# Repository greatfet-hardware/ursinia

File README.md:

# Ursinia
## a Grove base neighbor for GreatFET

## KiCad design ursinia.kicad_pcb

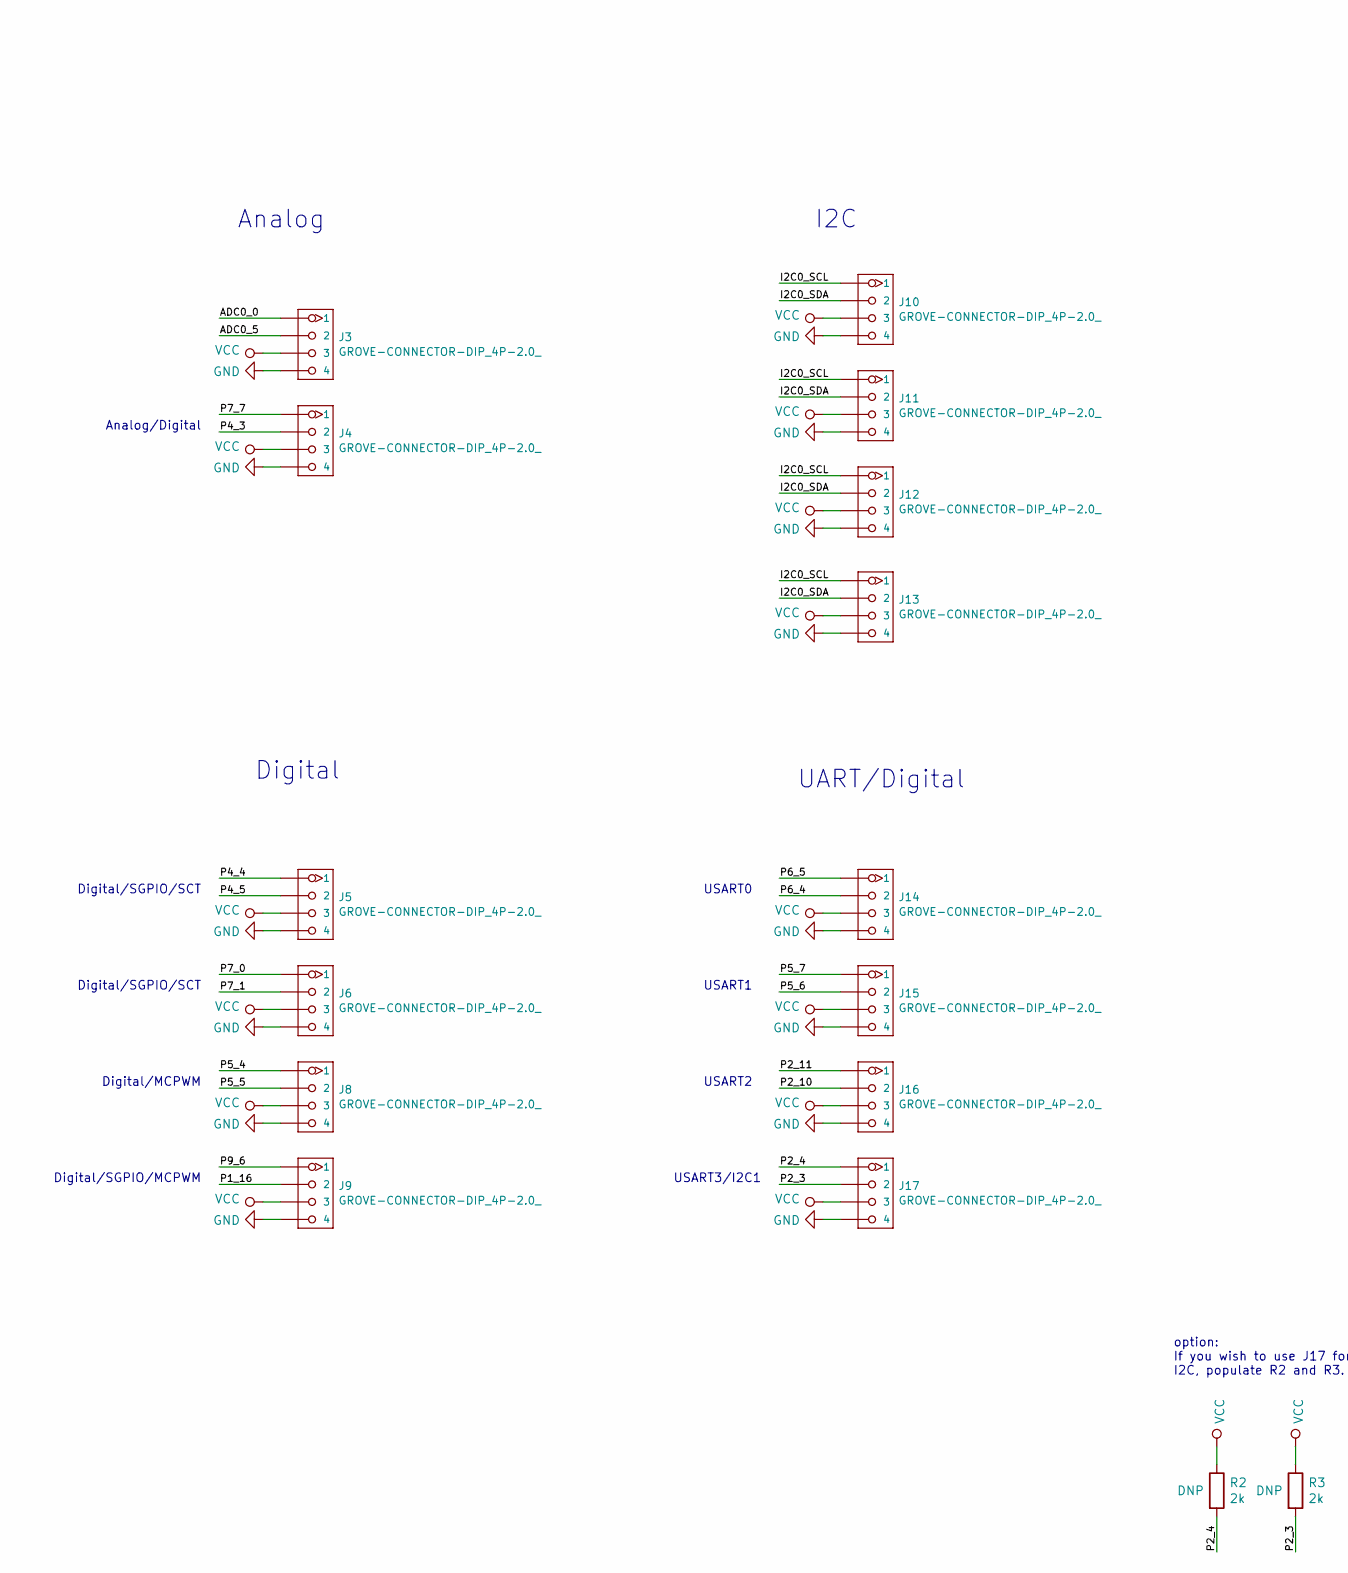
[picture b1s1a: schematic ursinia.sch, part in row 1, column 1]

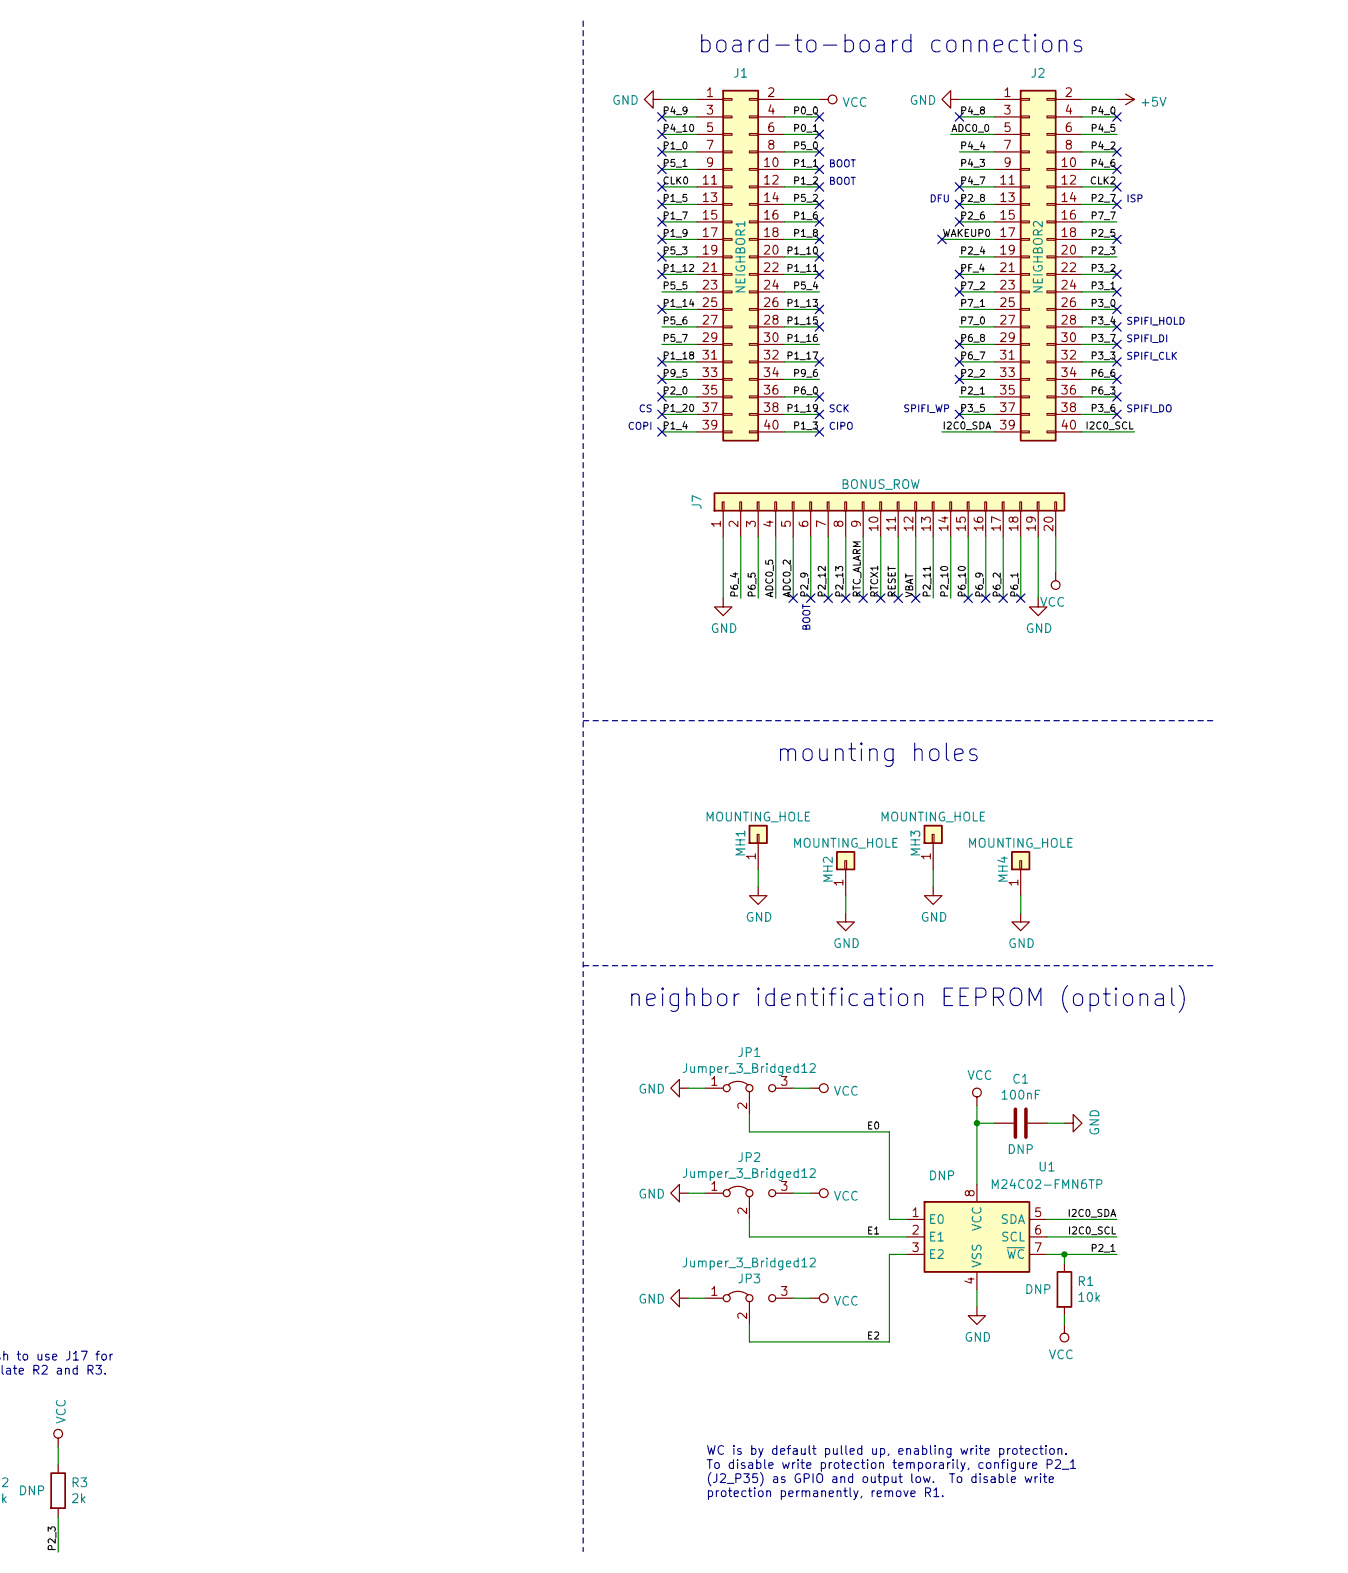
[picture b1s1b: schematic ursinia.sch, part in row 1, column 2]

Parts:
C1: 100nF; C_0603_1608Metric_Pad1.05x0.95mm_HandSolder
J1: NEIGHBOR1; HEADER-2x20; Part Number SSQ-120-23-G-D
J2: NEIGHBOR2; HEADER-2x20; Part Number SSQ-120-23-G-D
J3, J4, J9, J13, J17: GROVE-CONNECTOR-DIP_4P-2.0_; HW4-2.0-90D
J5, J6, J8, J10, J11, J12, J14, J15, J16: GROVE-CONNECTOR-DIP_4P-2.0_; HW4-2.0
J7: BONUS_ROW; HEADER-1x20; Part Number SSQ-120-23-G-S
JP1, JP2, JP3: Jumper_3_Bridged12; 0603-JUMPER-3-BRIDGED12
MH1, MH2, MH3, MH4: MOUNTING_HOLE; HOLE126MIL-COPPER
R1: 10k; R_0603_1608Metric_Pad1.05x0.95mm_HandSolder
R2, R3: 2k; R_0603_1608Metric_Pad1.05x0.95mm_HandSolder
U1: M24C02-FMN6TP; SOIC-8_3.9x4.9mm_P1.27mm

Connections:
+5V: J2.2
/ADC0_0: J2.5, J3.1
/ADC0_2: J7.5
/ADC0_5: J3.2, J7.4
/CLK0: J1.11
/CLK2: J2.12
/E0: JP1.2 (C), U1.1 (E0)
/E1: JP2.2 (C), U1.2 (E1)
/E2: JP3.2 (C), U1.3 (E2)
/I2C0_SCL: J2.40, J10.1, J11.1, J12.1, J13.1, U1.6 (SCL)
/I2C0_SDA: J2.39, J10.2, J11.2, J12.2, J13.2, U1.5 (SDA)
/P0_0: J1.4
/P0_1: J1.6
/P1_0: J1.7
/P1_1: J1.10
/P1_2: J1.12
/P1_3: J1.40
/P1_4: J1.39
/P1_5: J1.13
/P1_6: J1.16
/P1_7: J1.15
/P1_8: J1.18
/P1_9: J1.17
/P1_10: J1.20
/P1_11: J1.22
/P1_12: J1.21
/P1_13: J1.26
/P1_14: J1.25
/P1_15: J1.28
/P1_16: J1.30, J9.2
/P1_17: J1.32
/P1_18: J1.31
/P1_19: J1.38
/P1_20: J1.37
/P2_0: J1.35
/P2_1: J2.35, R1.1, U1.7 (~WC)
/P2_2: J2.33
/P2_3: J2.20, J17.2, R3.2
/P2_4: J2.19, J17.1, R2.2
/P2_5: J2.18
/P2_6: J2.15
/P2_7: J2.14
/P2_8: J2.13
/P2_9: J7.6
/P2_10: J7.14, J16.2
/P2_11: J7.13, J16.1
/P2_12: J7.7
/P2_13: J7.8
/P3_0: J2.26
/P3_1: J2.24
/P3_2: J2.22
/P3_3: J2.32
/P3_4: J2.28
/P3_5: J2.37
/P3_6: J2.38
/P3_7: J2.30
/P4_0: J2.4
/P4_2: J2.8
/P4_3: J2.9, J4.2
/P4_4: J2.7, J5.1
/P4_5: J2.6, J5.2
/P4_6: J2.10
/P4_7: J2.11
/P4_8: J2.3
/P4_9: J1.3
/P4_10: J1.5
/P5_0: J1.8
/P5_1: J1.9
/P5_2: J1.14
/P5_3: J1.19
/P5_4: J1.24, J8.1
/P5_5: J1.23, J8.2
/P5_6: J1.27, J15.2
/P5_7: J1.29, J15.1
/P6_0: J1.36
/P6_1: J7.18
/P6_2: J7.17
/P6_3: J2.36
/P6_4: J7.2, J14.2
/P6_5: J7.3, J14.1
/P6_6: J2.34
/P6_7: J2.31
/P6_8: J2.29
/P6_9: J7.16
/P6_10: J7.15
/P7_0: J2.27, J6.1
/P7_1: J2.25, J6.2
/P7_2: J2.23
/P7_7: J2.16, J4.1
/P9_5: J1.33
/P9_6: J1.34, J9.1
/PF_4: J2.21
/RESET: J7.11
/RTCX1: J7.10
/RTC_ALARM: J7.9
/VBAT: J7.12
/WAKEUP0: J2.17
GND: C1.1, J1.1, J2.1, J3.4, J4.4, J5.4, J6.4, J7.1, J7.19, J8.4, J9.4, J10.4, J11.4, J12.4, J13.4, J14.4, J15.4, J16.4, J17.4, JP1.1 (A), JP2.1 (A), JP3.1 (A), MH1.1, MH2.1, MH3.1, MH4.1, U1.4 (VSS)
VCC: C1.2, J1.2, J3.3, J4.3, J5.3, J6.3, J7.20, J8.3, J9.3, J10.3, J11.3, J12.3, J13.3, J14.3, J15.3, J16.3, J17.3, JP1.3 (B), JP2.3 (B), JP3.3 (B), R1.2, R2.1, R3.1, U1.8 (VCC)

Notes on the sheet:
CIPO
COPI
SCK
ISP
DFU
BOOT
WC is by default pulled up, enabling write protection. To disable write protection temporarily, configure P2_1 (J2_P35) as GPIO and output low. To disable write protection permanently, remove R1.
SPIFI_CLK
SPIFI_HOLD
SPIFI_WP
SPIFI_DO
SPIFI_DI
board-to-board connections
mounting holes
neighbor identification EEPROM (optional)
Analog
I2C
Digital
USART3/I2C1
USART2
USART1
USART0
UART/Digital
Analog/Digital
Digital/SGPIO/MCPWM
Digital/MCPWM
Digital/SGPIO/SCT
option: If you wish to use J17 for I2C, populate R2 and R3.

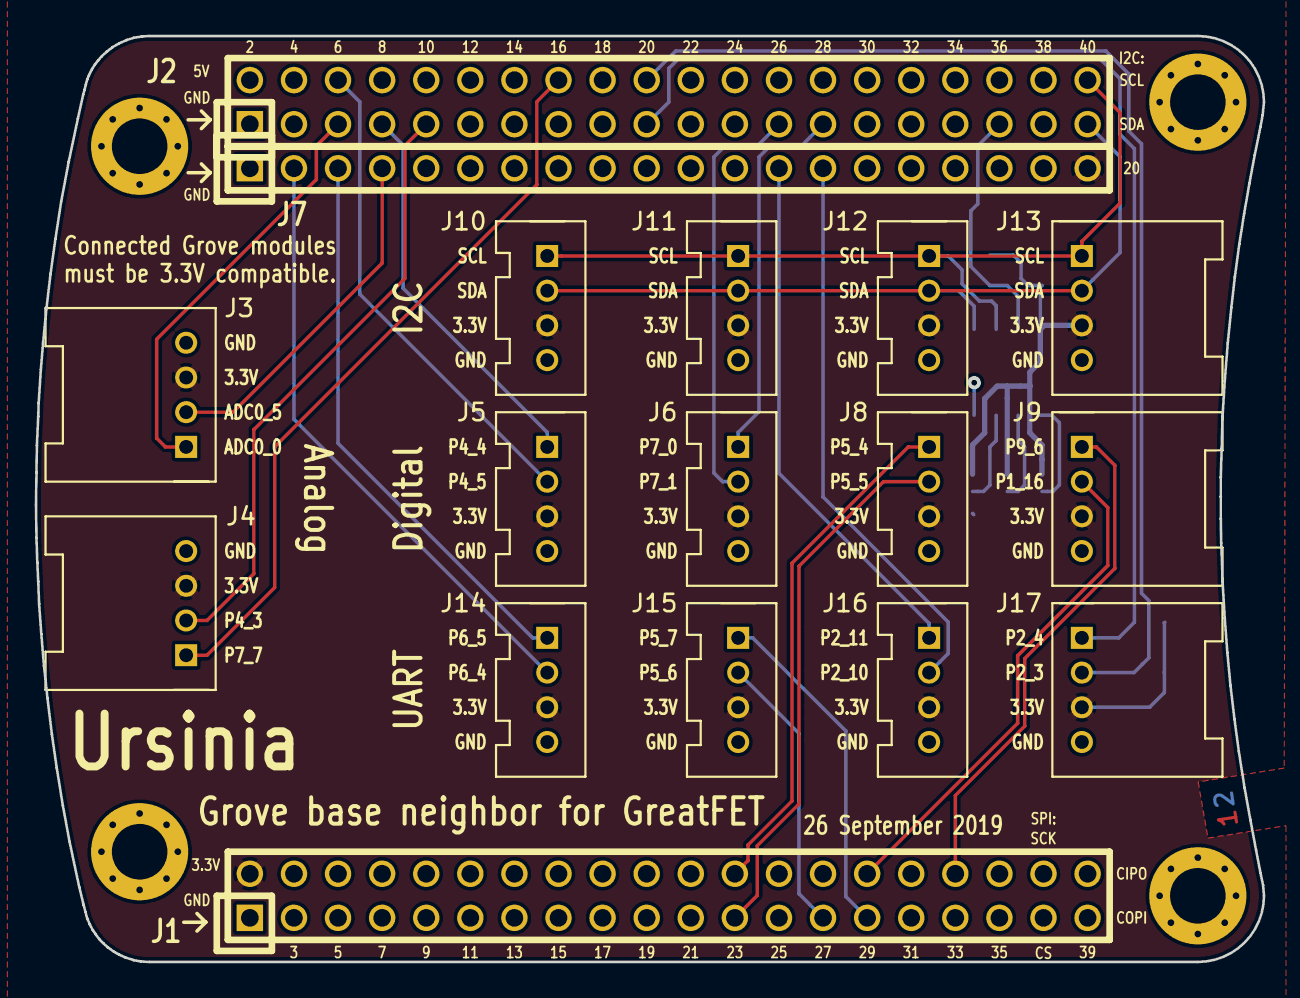
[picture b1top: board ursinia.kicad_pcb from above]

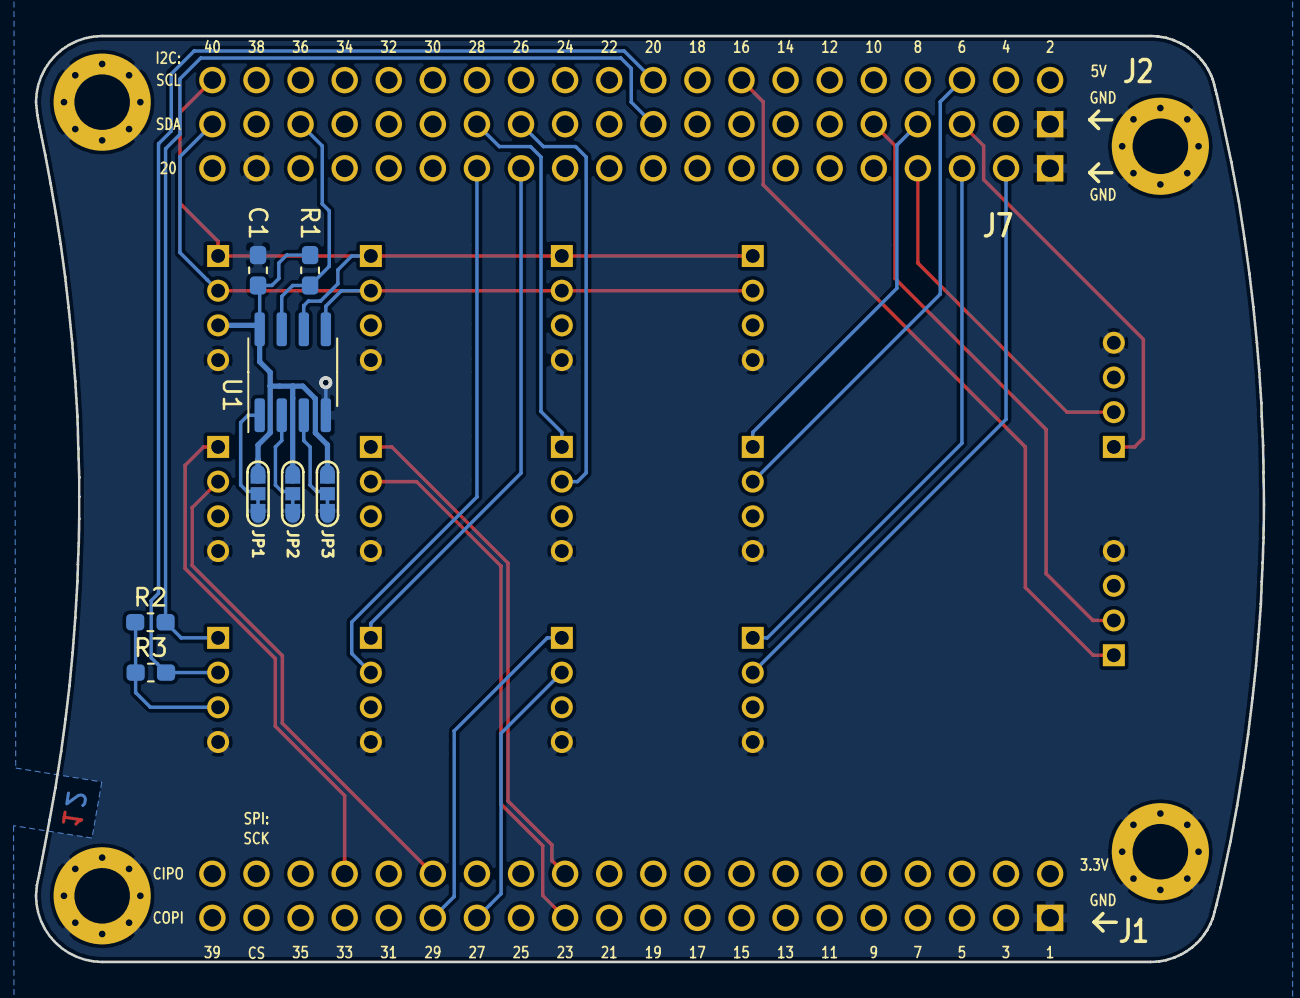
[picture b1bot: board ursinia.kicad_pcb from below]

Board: 2 copper layers, 70.7 x 53.3 mm, 29 parts (8 on the bottom side), 28 nets.

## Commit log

2019-09-25 initial commit based on neighbor-template
2019-09-25 add OPL_Kicad_Library submodule for Grove connectors
2019-09-26 complete design
2020-07-03 adopt OSHWA convention for SPI signal names https://www.oshwa.org/a-resolution-to-redefine-spi-signal-names
